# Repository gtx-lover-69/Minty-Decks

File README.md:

# Minty Decks!
These are two really cool *(literally)* pocket sized cyberdecks based on the ESP32-C3 and ESP32-S3.

The V1 was unfortunately designed quite shittily with 2mm spacing and holes, rather than 2.54mm.
The V2 or Pro aimed to solve that problem AND added more features like an RGB LED, a bunch more breakout, and a micro SD card slot.

# A story about a waste of 15 Euro
I was so proud of myself for the V1 that immediately upon finishing the PCB, I ordered it via JLCPCB. What a mistake.

# Some renders
P.S. You can experience it for yourself in 3D [here](https://3dviewer.net/#model=https://github.com/gtx-lover-69/Minty-Decks/blob/main/minty_deck/minty_deck.step,https://github.com/gtx-lover-69/Minty-Decks/blob/main/minty_deck/minty_deck_2/minty_deck_2.step)
Before

After

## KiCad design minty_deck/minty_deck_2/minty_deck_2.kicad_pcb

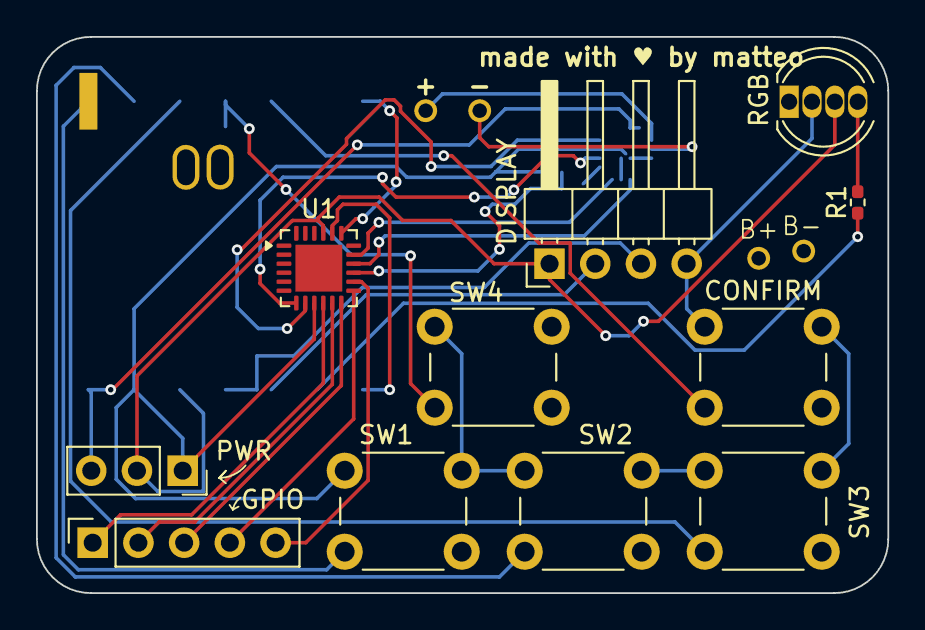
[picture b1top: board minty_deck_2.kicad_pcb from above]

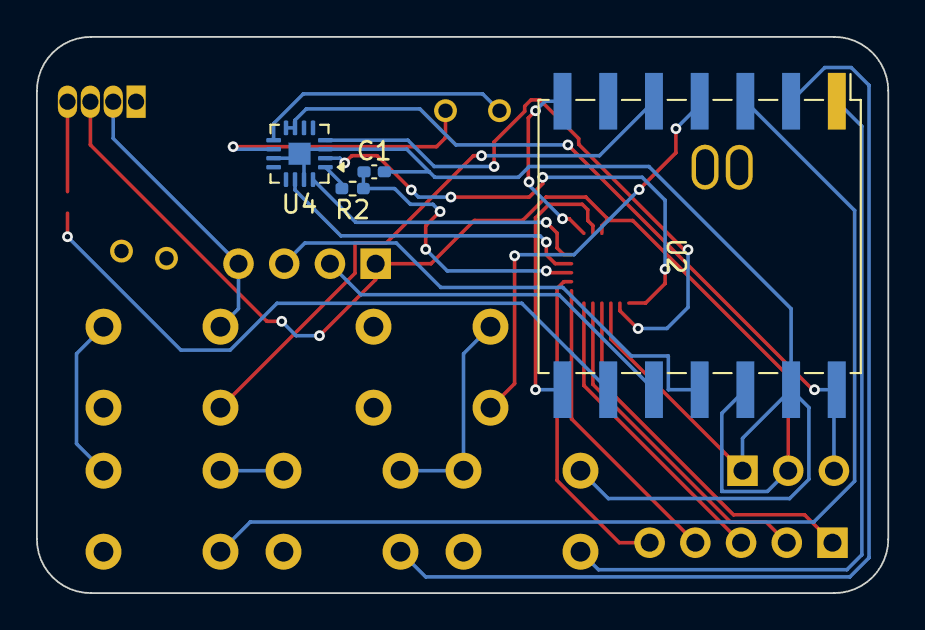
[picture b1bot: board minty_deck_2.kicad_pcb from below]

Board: 2 copper layers, 47.3 x 30.9 mm, 19 parts (4 on the bottom side), 27 nets.

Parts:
+: Conn_01x01_Socket; Untitled
-: Conn_01x01_Socket; Untitled
B+: Conn_01x01_Socket; Untitled
B-: Conn_01x01_Socket; Untitled
C1: 1uF; C_0402_1005Metric_Pad0.74x0.62mm_HandSolder
CONFIRM: SW_Push; SW_PUSH_6mm
DISPLAY: Conn_01x04_Pin; PinHeader_1x04_P2.54mm_Horizontal
GPIO: Conn_01x05_Socket; PinSocket_1x05_P2.54mm_Vertical
PWR: Conn_01x03_Socket; PinSocket_1x03_P2.54mm_Vertical
R1, R2: 150; R_0402_1005Metric_Pad0.72x0.64mm_HandSolder
RGB: NeoPixel_THT; LED_D5.0mm-4_RGB
SW1, SW2, SW3, SW4: SW_Push; SW_PUSH_6mm
U1: STMPE1600; QFN-24-1EP_4x4mm_P0.5mm_EP2.6x2.6mm
U2: XIAO_ESP32_S3; xiao_esp32c3
U4: MAX98357A; TQFN-16-1EP_3x3mm_P0.5mm_EP1.23x1.23mm

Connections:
+3V3: DISPLAY.1, PWR.2, RGB.3 (VDD), U1.21 (VCC), U2.12 (3V3)
+5V: PWR.3, U2.14 (5V), U4.7 (VDD), U4.8 (VDD)
BCLK: U1.17 (GPIO_15), U4.16 (BCLK)
CONFIRM: CONFIRM.2, U2.5 (D4/GPIO5)
GAIN: U1.7 (GPIO_6), U4.2 (GAIN_SLOT)
GND: C1.2, CONFIRM.1, DISPLAY.4, PWR.1, RGB.2 (GND), SW1.1, SW2.1, SW3.1, SW4.1, U1.9 (GND), U2.13 (GND), U4.3 (GND), U4.11 (GND), U4.15 (GND), U4.17 (PAD)
GPIO_8: GPIO.1, U1.10 (GPIO_8)
GPIO_9: GPIO.2, U1.11 (GPIO_9)
GPIO_10: GPIO.3, U1.12 (GPIO_10)
GPIO_11: GPIO.4, U1.13 (GPIO_11)
GPIO_12: GPIO.5, U1.14 (GPIO_12)
LRCLK: U1.16 (GPIO_14), U4.14 (LRCLK)
NEO: R1.1, U2.9 (D8/GPIO7)
unnamed: R1.2, RGB.4 (DIN)
unnamed: +.1 (Pin_1_1), U4.9 (OUTP)
unnamed: -.1 (Pin_1_1), U4.10 (OUTN)
unnamed: U1.19 (SCL), U2.7 (D6/GPIO43)
unnamed: U1.20 (SDA), U2.8 (D7/GPIO44)
unnamed: R2.2, U4.1 (DIN)
SCL: DISPLAY.3, U2.11 (D10/GPIO9)
SD: U1.8 (GPIO_7), U4.4 (~SD_MODE)
SDA: DISPLAY.2, U2.10 (D9/GPIO8)
SPEAKER: C1.1, R2.1, U1.15 (GPIO_13)
SW1: SW1.2, U2.1 (D0/GPIO1)
SW2: SW2.2, U2.2 (D1/GPIO2)
SW3: SW3.2, U2.3 (D2/GPIO3)
SW4: SW4.2, U2.4 (D3/GPIO4)

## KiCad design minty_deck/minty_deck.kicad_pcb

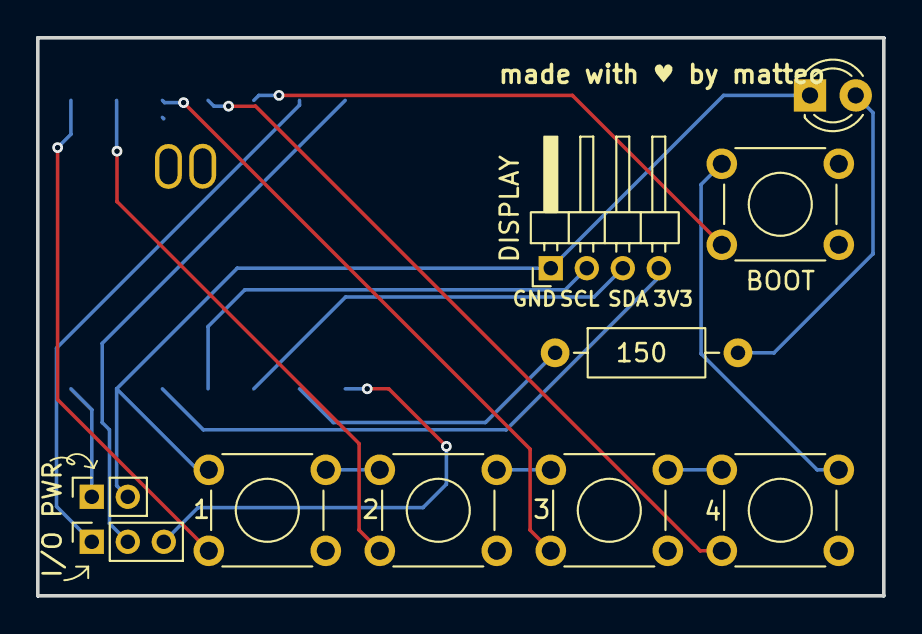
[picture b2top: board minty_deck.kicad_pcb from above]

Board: 2 copper layers, 47.0 x 31.0 mm, 11 parts (1 on the bottom side), 15 nets.

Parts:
D1: LED; LED_D3.0mm
J1: PWR; PinSocket_1x02_P2.00mm_Vertical
J2: I/O; PinSocket_1x03_P2.00mm_Vertical
J3: DISPLAY; PinHeader_1x04_P2.00mm_Horizontal
R1: 150; R_Axial_DIN0207_L6.3mm_D2.5mm_P10.16mm_Horizontal
SW1: 1; SW_TH_Tactile_Omron_B3F-100x
SW2: 2; SW_TH_Tactile_Omron_B3F-100x
SW3: 3; SW_TH_Tactile_Omron_B3F-100x
SW4: 4; SW_TH_Tactile_Omron_B3F-100x
SW5: BOOT; SW_TH_Tactile_Omron_B3F-100x
U1: XIAO ESP32C3; xiao_esp32c3

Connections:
+3.3V: J3.4, U1.12 (VCC_3V3)
+5V: J1.1, U1.14 (VUSB)
BOTTOM: SW2.2, U1.2 (D1)
CONFIRM: SW5.2, U1.5 (D4)
D5: J2.1, U1.6 (D5)
D6: J2.2, U1.7 (D6)
D7: J2.3, U1.8 (D7)
GND: D1.1 (K), J1.2, J3.1, SW1.1, SW2.1, SW3.1, SW4.1, SW5.1, U1.13 (GND)
LEFT: SW3.2, U1.3 (D2)
unnamed: D1.2 (A), R1.2
unnamed: R1.1, U1.9 (D8)
RIGHT: SW4.2, U1.4 (D3)
SCL: J3.2, U1.11 (D10)
SDA: J3.3, U1.10 (D9)
TOP: SW1.2, U1.1 (D0)
